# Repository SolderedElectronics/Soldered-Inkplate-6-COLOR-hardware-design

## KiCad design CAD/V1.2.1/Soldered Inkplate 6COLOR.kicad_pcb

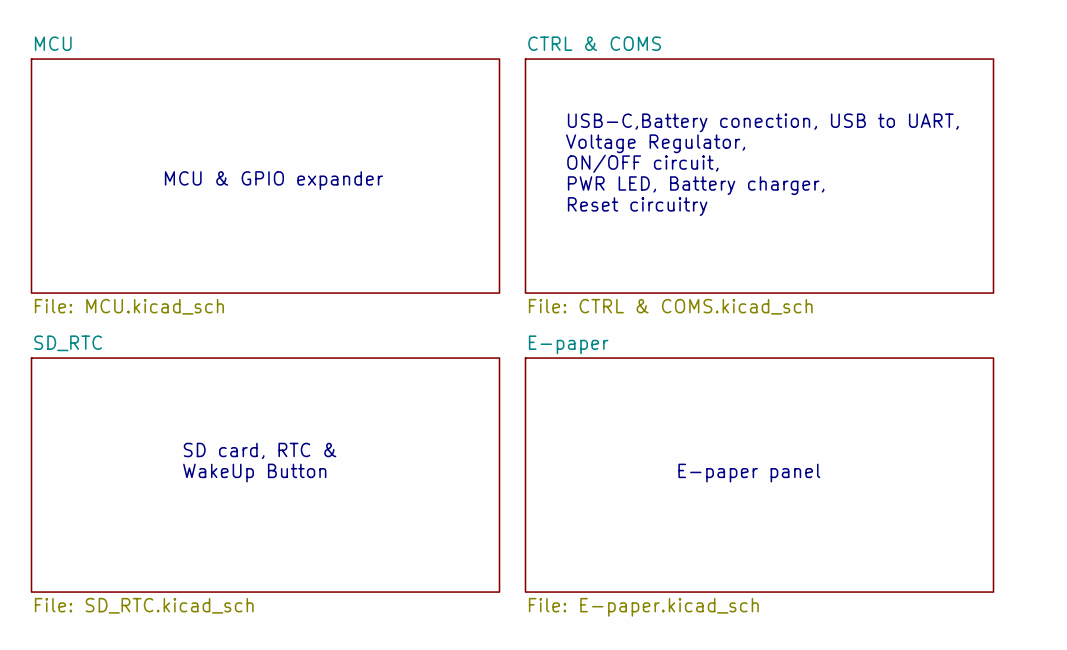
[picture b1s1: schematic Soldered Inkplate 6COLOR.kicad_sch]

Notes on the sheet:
MCU & GPIO expander
SD card, RTC & WakeUp Button
USB-C,Battery conection, USB to UART, Voltage Regulator, ON/OFF circuit, PWR LED, Battery charger, Reset circuitry
E-paper panel

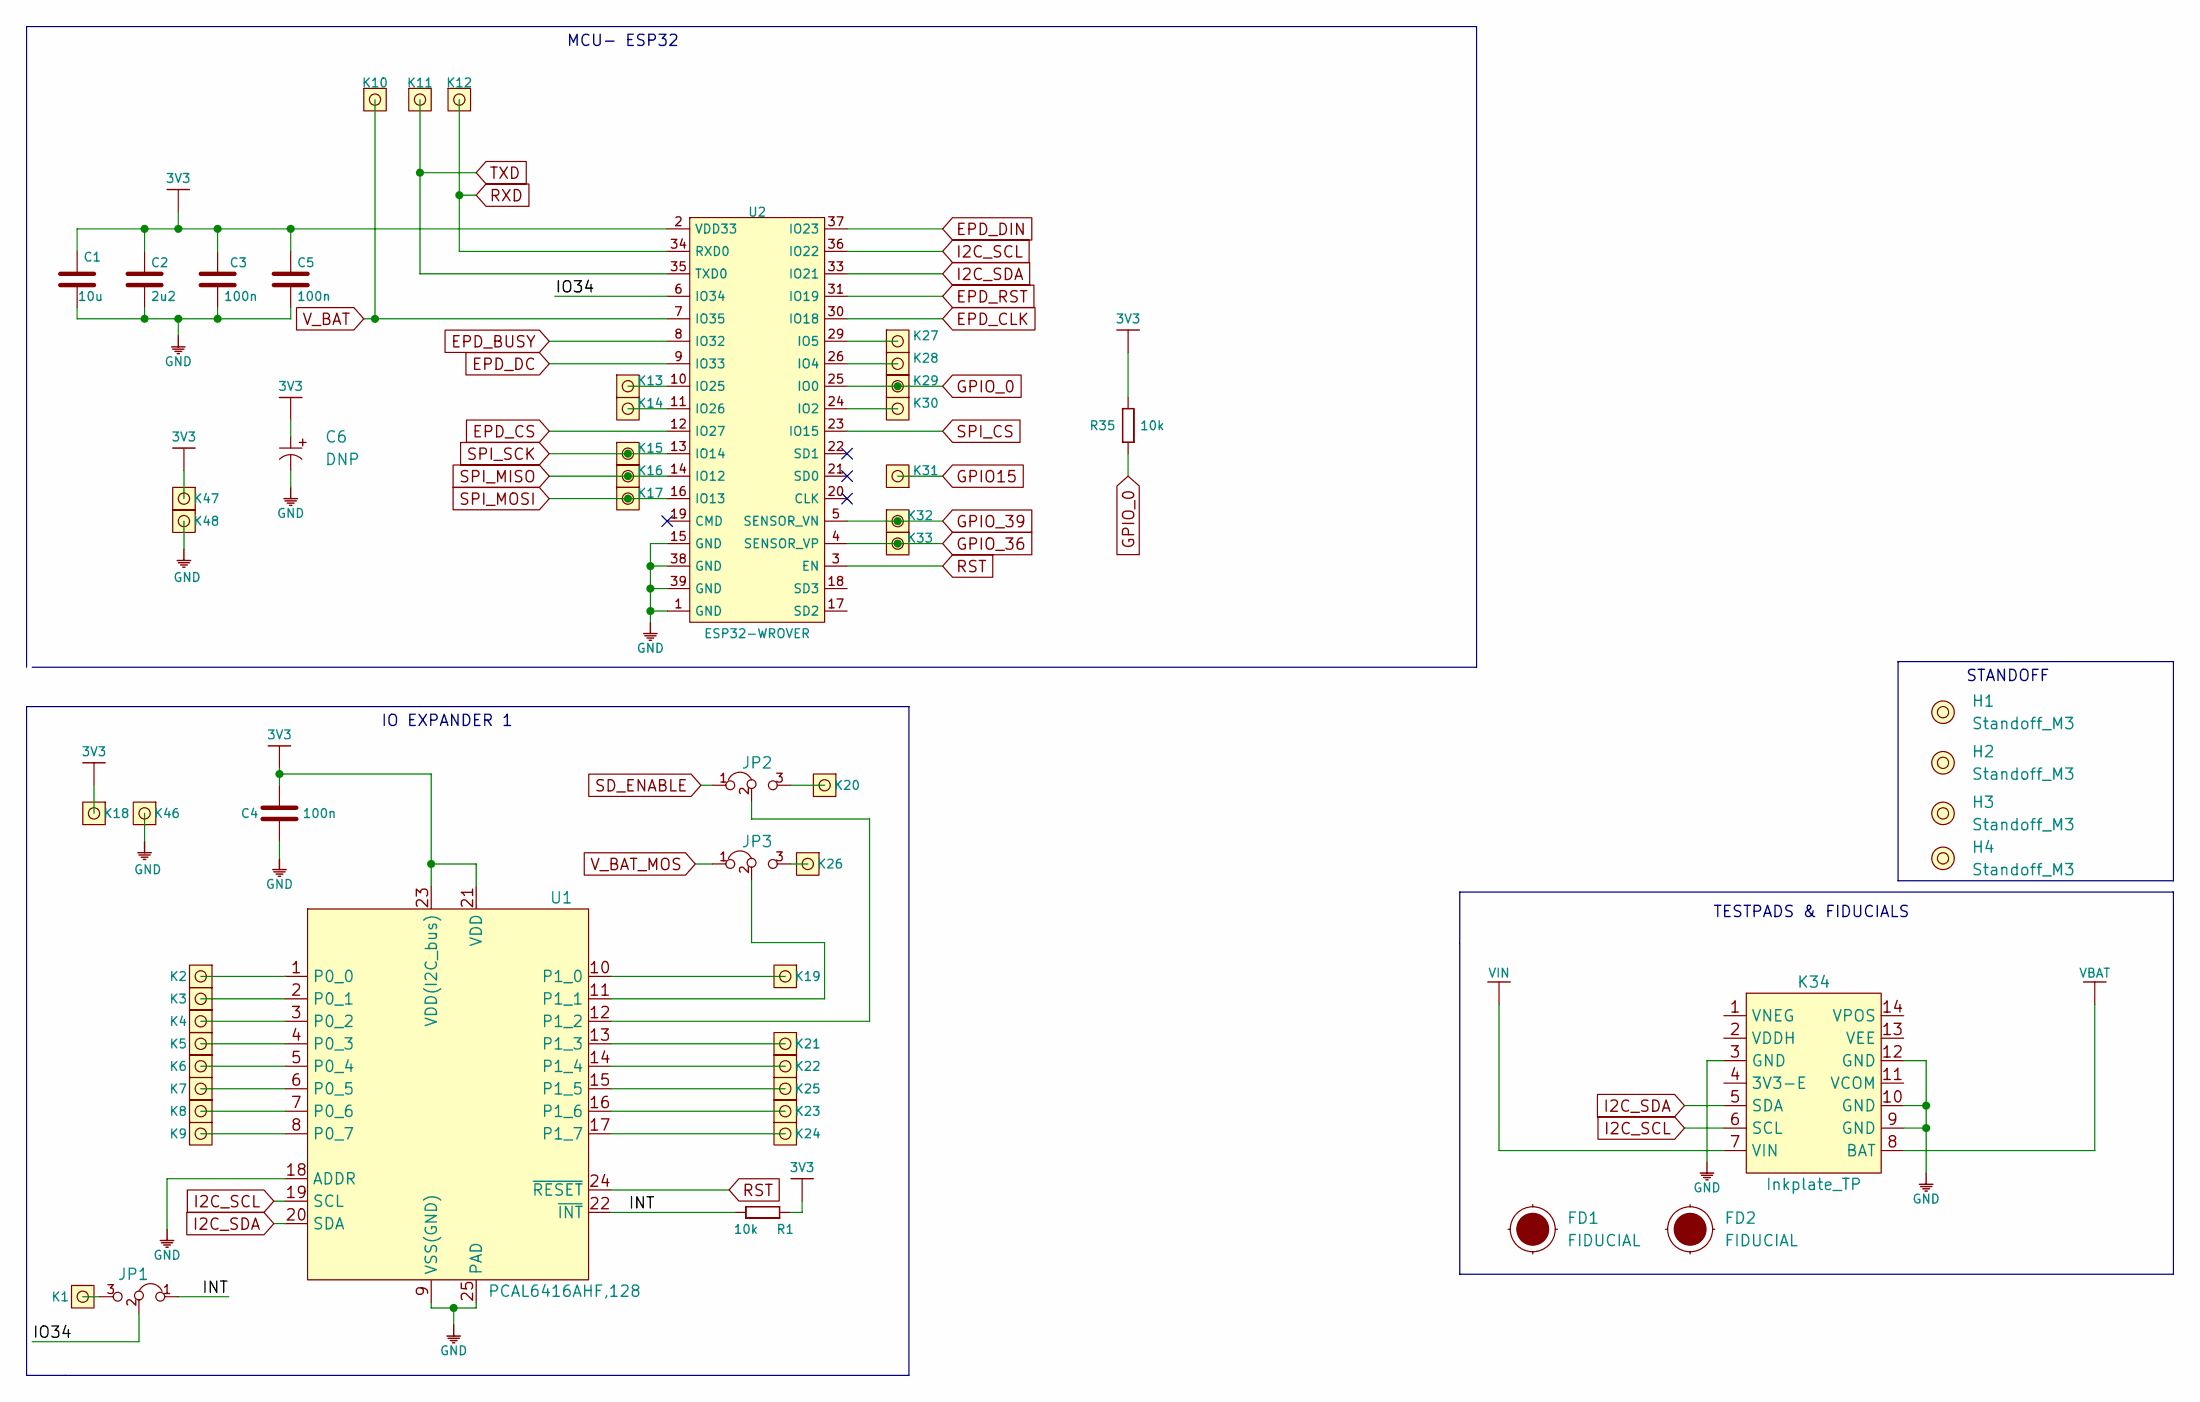
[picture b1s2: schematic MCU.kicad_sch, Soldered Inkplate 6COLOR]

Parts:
C1: 10u; 1206C
C2: 2u2; 0603C
C3, C4, C5: 100n; 0603C
C6: DNP; 2917C
FD1, FD2: FIDUCIAL; FIDUCIAL_23
H1, H2, H3, H4: Standoff_M3
JP1, JP2, JP3: SMD_JUMPER_3_PAD_CONNECTED_LEFT_TRACE
K1, K2, K3, K4, K5, K6, K7, K8, K9, K10, K11, K12, K13, K14, K15, K16, K17, K18, K19, K20, K21, K22, K23, K24, K25, K26, K27, K28, K29, K30, K31, K32, K33, K46, K47, K48: HEADER_MALE_1X1_Inkplate
K34: Inkplate_TP; INKPLATE TEST HEADER
R1, R35: 10k; 0603R
U1: PCAL6416AHF,128
U2: ESP32-WROVER

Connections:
3V3: C1.2, C2.2, C3.2, C4.2, C5.2, C6.1 (+), K18.1, K47.1, R1.1, R35.2, U1.21 (VDD), U1.23 (VDD(I2C_bus)), U2.2 (VDD33); also elsewhere on the board
/MCU/INT: JP1.1, R1.2, U1.22 (~INT)
/MCU/IO34: JP1.2, U2.6 (IO34)
EPD_BUSY: U2.8 (IO32); also elsewhere on the board
EPD_CLK: U2.30 (IO18); also elsewhere on the board
EPD_CS: U2.12 (IO27); also elsewhere on the board
EPD_DC: U2.9 (IO33); also elsewhere on the board
EPD_DIN: U2.37 (IO23); also elsewhere on the board
EPD_RST: U2.31 (IO19); also elsewhere on the board
GND: C1.1, C2.1, C3.1, C4.1, C5.1, C6.2 (-), K34.3 (GND), K34.9 (GND), K34.10 (GND), K34.12 (GND), K46.1, K48.1, U1.9 (VSS(GND)), U1.18 (ADDR), U1.25 (PAD), U2.1 (GND), U2.15 (GND), U2.38 (GND), U2.39 (GND); also elsewhere on the board
GPIO15: K31.1; also elsewhere on the board
GPIO_0: K29.1, R35.1, U2.25 (IO0); also elsewhere on the board
GPIO_36: K33.1, U2.4 (SENSOR_VP); also elsewhere on the board
GPIO_39: K32.1, U2.5 (SENSOR_VN); also elsewhere on the board
I2C_SCL: K34.6 (SCL), U1.19 (SCL), U2.36 (IO22); also elsewhere on the board
I2C_SDA: K34.5 (SDA), U1.20 (SDA), U2.33 (IO21); also elsewhere on the board
unnamed: JP1.3, K1.1
unnamed: JP2.2, U1.12 (P1_2)
unnamed: JP2.3, K20.1
unnamed: JP3.2, U1.11 (P1_1)
unnamed: JP3.3, K26.1
unnamed: K2.1, U1.1 (P0_0)
unnamed: K3.1, U1.2 (P0_1)
unnamed: K4.1, U1.3 (P0_2)
unnamed: K5.1, U1.4 (P0_3)
unnamed: K6.1, U1.5 (P0_4)
unnamed: K7.1, U1.6 (P0_5)
unnamed: K8.1, U1.7 (P0_6)
unnamed: K9.1, U1.8 (P0_7)
unnamed: K13.1, U2.10 (IO25)
unnamed: K14.1, U2.11 (IO26)
unnamed: K19.1, U1.10 (P1_0)
unnamed: K21.1, U1.13 (P1_3)
unnamed: K22.1, U1.14 (P1_4)
unnamed: K23.1, U1.16 (P1_6)
unnamed: K24.1, U1.17 (P1_7)
unnamed: K25.1, U1.15 (P1_5)
unnamed: K27.1, U2.29 (IO5)
unnamed: K28.1, U2.26 (IO4)
unnamed: K30.1, U2.24 (IO2)
RST: U1.24 (~RESET), U2.3 (EN); also elsewhere on the board
RXD: K12.1, U2.34 (RXD0); also elsewhere on the board
SD_ENABLE: JP2.1; also elsewhere on the board
SPI_CS: U2.23 (IO15); also elsewhere on the board
SPI_MISO: K16.1, U2.14 (IO12); also elsewhere on the board
SPI_MOSI: K17.1, U2.16 (IO13); also elsewhere on the board
SPI_SCK: K15.1, U2.13 (IO14); also elsewhere on the board
TXD: K11.1, U2.35 (TXD0); also elsewhere on the board
VBAT: K34.8 (BAT); also elsewhere on the board
VIN: K34.7 (VIN); also elsewhere on the board
V_BAT: K10.1, U2.7 (IO35); also elsewhere on the board
V_BAT_MOS: JP3.1; also elsewhere on the board

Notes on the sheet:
IO EXPANDER 1
MCU- ESP32
TESTPADS & FIDUCIALS
STANDOFF

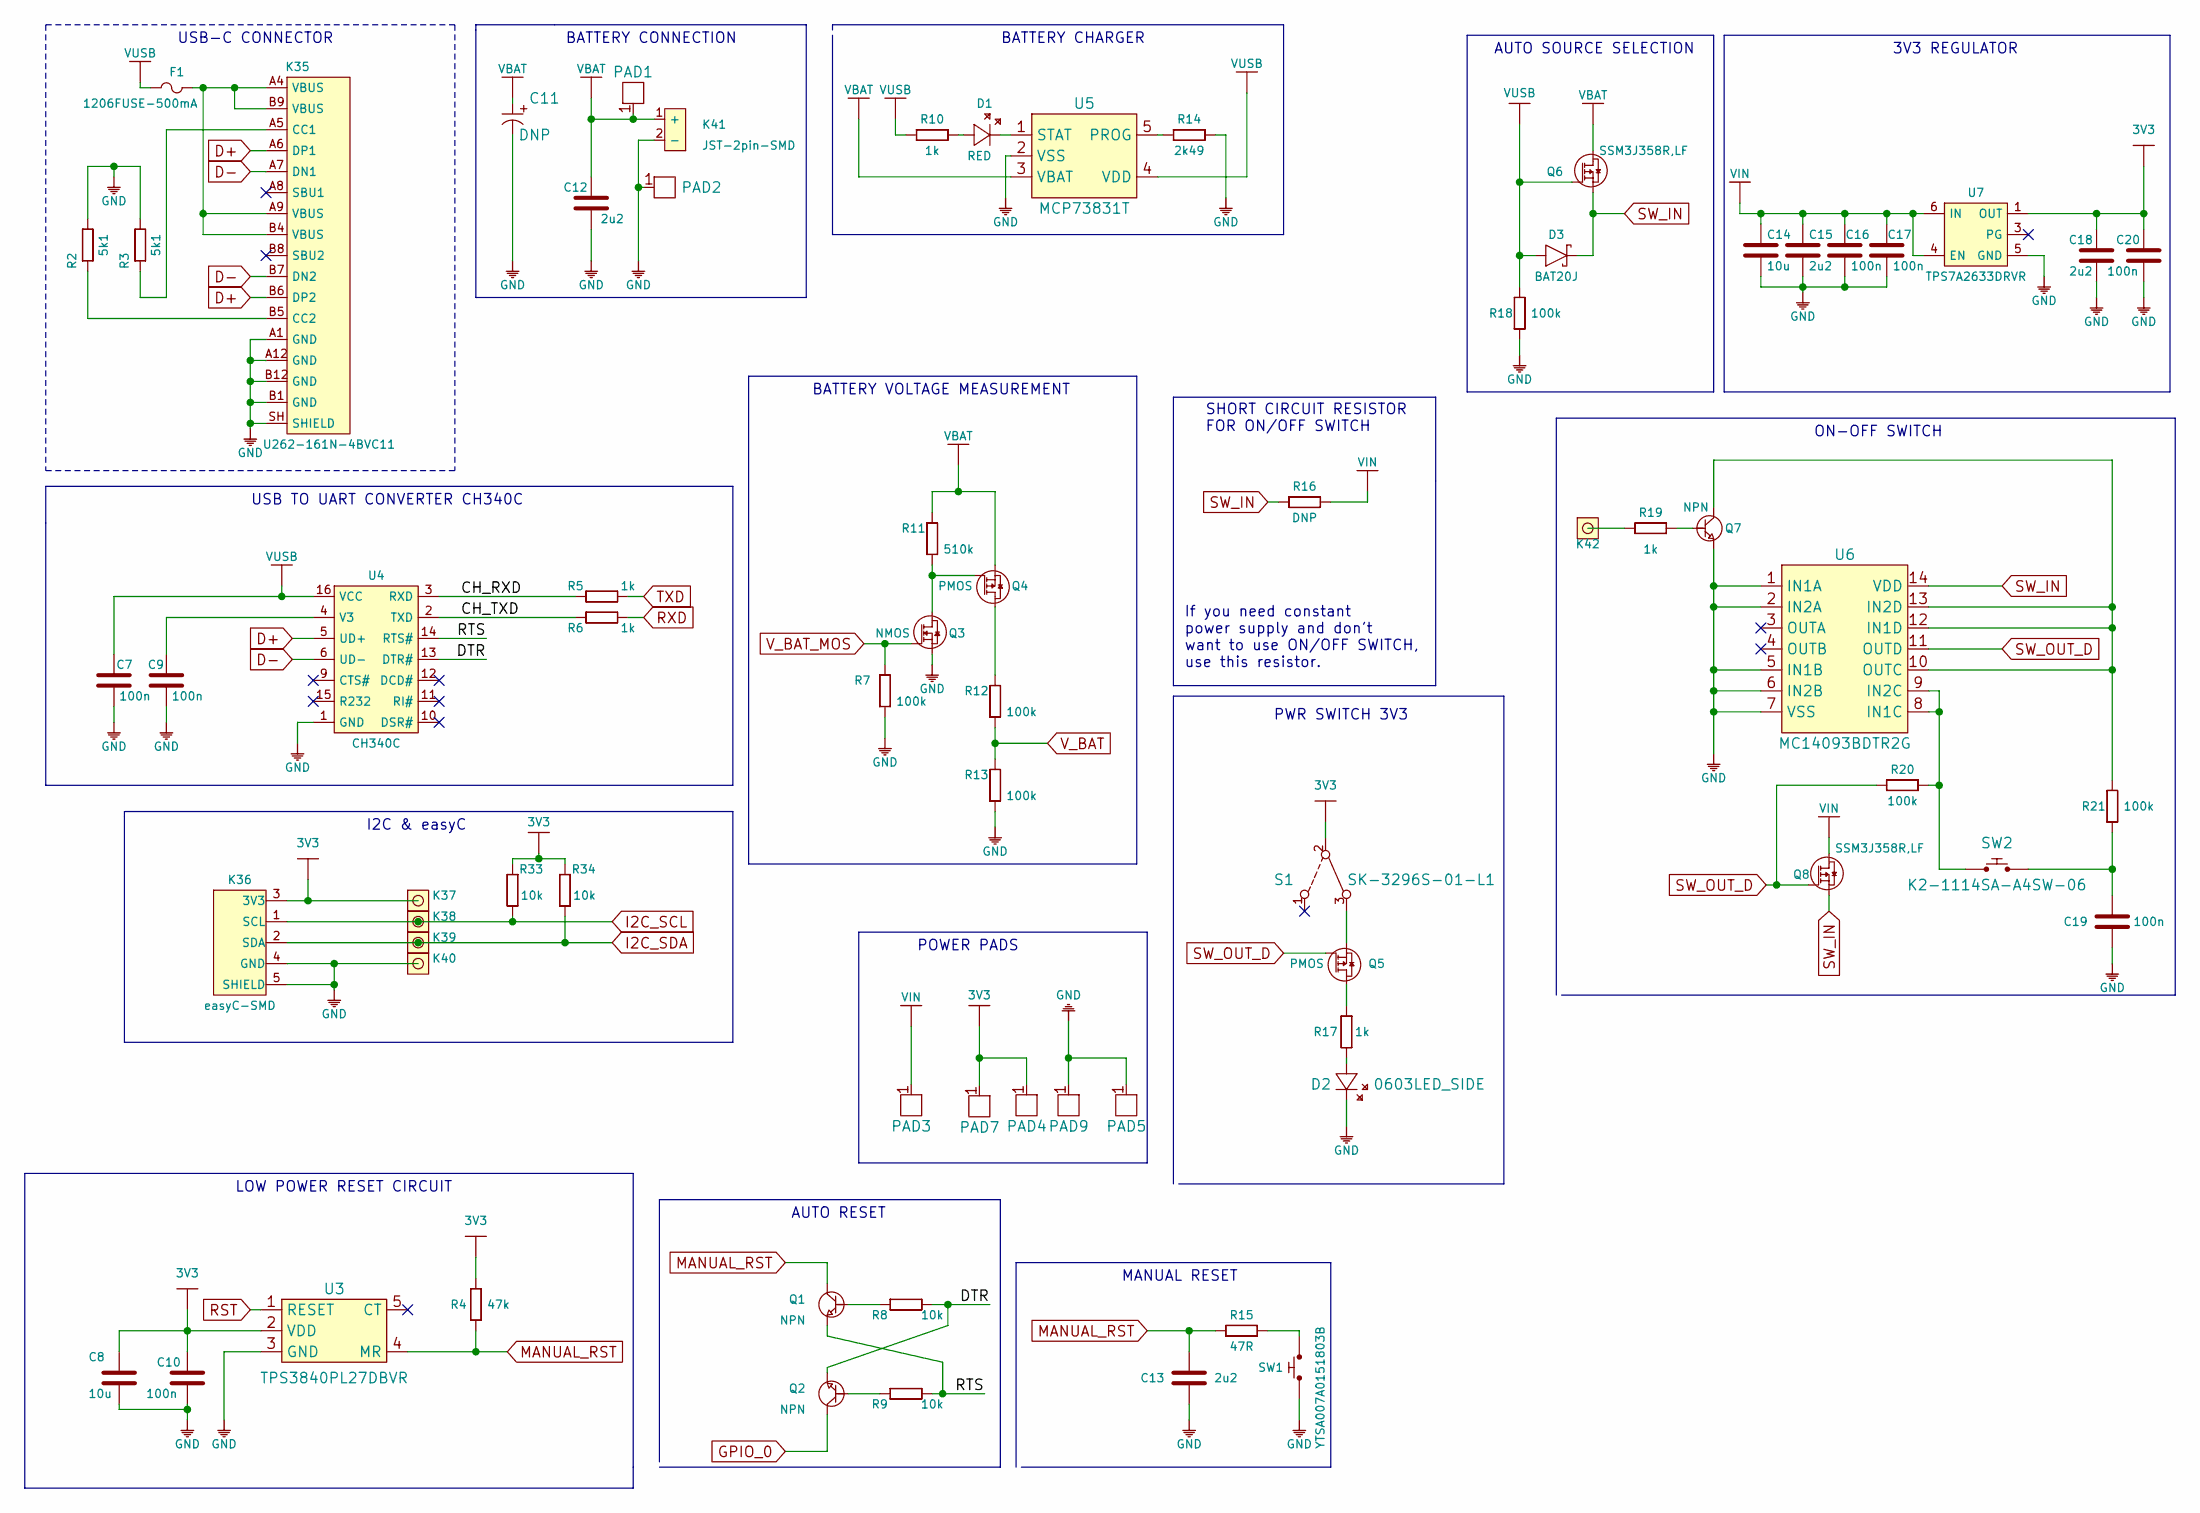
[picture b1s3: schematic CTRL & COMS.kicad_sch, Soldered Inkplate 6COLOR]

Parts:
C7, C9, C10, C16, C17, C19, C20: 100n; 0603C
C8, C14: 10u; 1206C
C11: DNP; 2917C
C12, C13, C15, C18: 2u2; 0603C
D1: RED; 0402LED
D2: 0603LED_SIDE; LTST-S270GKT
D3: BAT20J; SOD-323
F1: 1206FUSE-500mA; 1206FUSE
K35: U262-161N-4BVC11
K36: easyC-SMD; easyC-connector
K37, K38, K39, K40, K42: HEADER_MALE_1X1_Inkplate
K41: JST-2pin-SMD
PAD1, PAD2, PAD3, PAD4, PAD5, PAD7, PAD9: PAD_4x4
Q1, Q2, Q7: NPN; SOT-23-3
Q3: NMOS; SOT-23-3
Q4, Q5: PMOS; SOT-23-3
Q6, Q8: SSM3J358R,LF; SOT-23-3
R2, R3: 5k1; 0603R
R4: 47k; 0603R
R5, R6, R10, R17, R19: 1k; 0603R
R7, R12, R13, R18, R20, R21: 100k; 0603R
R8, R9, R33, R34: 10k; 0603R
R11: 510k; 0603R
R14: 2k49; 0603R
R15: 47R; 0603R
R16: DNP; 0603R
S1: SK-3296S-01-L1
SW1: YTSA007A0151803B
SW2: K2-1114SA-A4SW-06
U3: TPS3840PL27DBVR; SOT-23-5
U4: CH340C; SOP-16
U5: MCP73831T; SOT-23-5
U6: MC14093BDTR2G; TSSOP-14
U7: TPS7A2633DRVR

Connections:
3V3: C8.2, C10.2, C18.2, C20.2, K36.3 (3V3), K37.1, PAD4.1, PAD7.1, R4.2, R33.1, R34.1, S1.2, U3.2 (VDD), U7.1 (OUT); also elsewhere on the board
/CTRL & COMS/CH_RXD: R5.1, U4.3 (RXD)
/CTRL & COMS/CH_TXD: R6.1, U4.2 (TXD)
/CTRL & COMS/DTR: Q2.2 (E), R8.2, U4.13 (DTR#)
/CTRL & COMS/RTS: Q1.2 (E), R9.2, U4.14 (RTS#)
D+: K35.A6 (DP1), K35.B6 (DP2), U4.5 (UD+)
D-: K35.A7 (DN1), K35.B7 (DN2), U4.6 (UD-)
GND: C7.1, C8.1, C9.1, C10.1, C11.2 (-), C12.1, C13.1, C14.1, C15.1, C16.1, C17.1, C18.1, C19.1, C20.1, D2.2 (K), K35.A1 (GND), K35.A12 (GND), K35.B1 (GND), K35.B12 (GND), K35.SH (SHIELD), K36.4 (GND), K36.5 (SHIELD), K40.1, K41.2 (-), PAD2.1, PAD5.1, PAD9.1, Q3.2 (S), Q7.2 (E), R2.2, R3.2, R7.1, R13.1, R14.2, R18.1, SW1.1, U3.3 (GND), U4.1 (GND), U5.2 (VSS), U6.1 (IN1A), U6.2 (IN2A), U6.5 (IN1B), U6.6 (IN2B), U6.7 (VSS), U7.5 (GND); also elsewhere on the board
GPIO_0: Q2.3 (C); also elsewhere on the board
I2C_SCL: K36.1 (SCL), K38.1, R33.2; also elsewhere on the board
I2C_SDA: K36.2 (SDA), K39.1, R34.2; also elsewhere on the board
MANUAL_RST: C13.2, Q1.3 (C), R4.1, R15.2, U3.4 (MR)
unnamed: C9.2, U4.4 (V3)
unnamed: C19.2, R21.1, SW2.2
unnamed: D1.1 (A), R10.2
unnamed: D1.2 (K), U5.1 (STAT)
unnamed: D2.1 (A), R17.2
unnamed: F1.2, K35.A4 (VBUS), K35.A9 (VBUS), K35.B4 (VBUS), K35.B9 (VBUS)
unnamed: K35.A5 (CC1), R3.1
unnamed: K35.B5 (CC2), R2.1
unnamed: K42.1, R19.2
unnamed: Q1.1 (B), R8.1
unnamed: Q2.1 (B), R9.1
unnamed: Q3.3 (D), Q4.1 (G), R11.1
unnamed: Q4.3 (D), R12.2
unnamed: Q5.2 (S), S1.3
unnamed: Q5.3 (D), R17.1
unnamed: Q7.1 (B), R19.1
unnamed: Q7.3 (C), R21.2, U6.10 (OUTC), U6.12 (IN1D), U6.13 (IN2D)
unnamed: R14.1, U5.5 (PROG)
unnamed: R15.1, SW1.2
unnamed: R20.1, SW2.1, U6.8 (IN1C), U6.9 (IN2C)
RST: U3.1 (RESET); also elsewhere on the board
RXD: R6.2; also elsewhere on the board
SW_IN: D3.2 (C), Q6.2 (S), Q8.2 (S), R16.1, U6.14 (VDD)
SW_OUT_D: Q5.1 (G), Q8.1 (G), R20.2, U6.11 (OUTD)
TXD: R5.2; also elsewhere on the board
VBAT: C11.1 (+), C12.2, K41.1 (+), PAD1.1, Q4.2 (S), Q6.3 (D), R11.2, U5.3 (VBAT); also elsewhere on the board
VIN: C14.2, C15.2, C16.2, C17.2, PAD3.1, Q8.3 (D), R16.2, U7.4 (EN), U7.6 (IN); also elsewhere on the board
VUSB: C7.2, D3.1 (A), F1.1, Q6.1 (G), R10.1, R18.2, U4.16 (VCC), U5.4 (VDD)
V_BAT: R12.1, R13.2; also elsewhere on the board
V_BAT_MOS: Q3.1 (G), R7.2; also elsewhere on the board

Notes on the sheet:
AUTO RESET
LOW POWER RESET CIRCUIT
ON-OFF SWITCH
POWER PADS
SHORT CIRCUIT RESISTOR FOR ON/OFF SWITCH
3V3 REGULATOR
USB TO UART CONVERTER CH340C
BATTERY VOLTAGE MEASUREMENT
If you need constant power supply and don't want to use ON/OFF SWITCH, use this resistor.
BATTERY CONNECTION
MANUAL RESET
PWR SWITCH 3V3
USB-C CONNECTOR
AUTO SOURCE SELECTION
I2C & easyC
BATTERY CHARGER

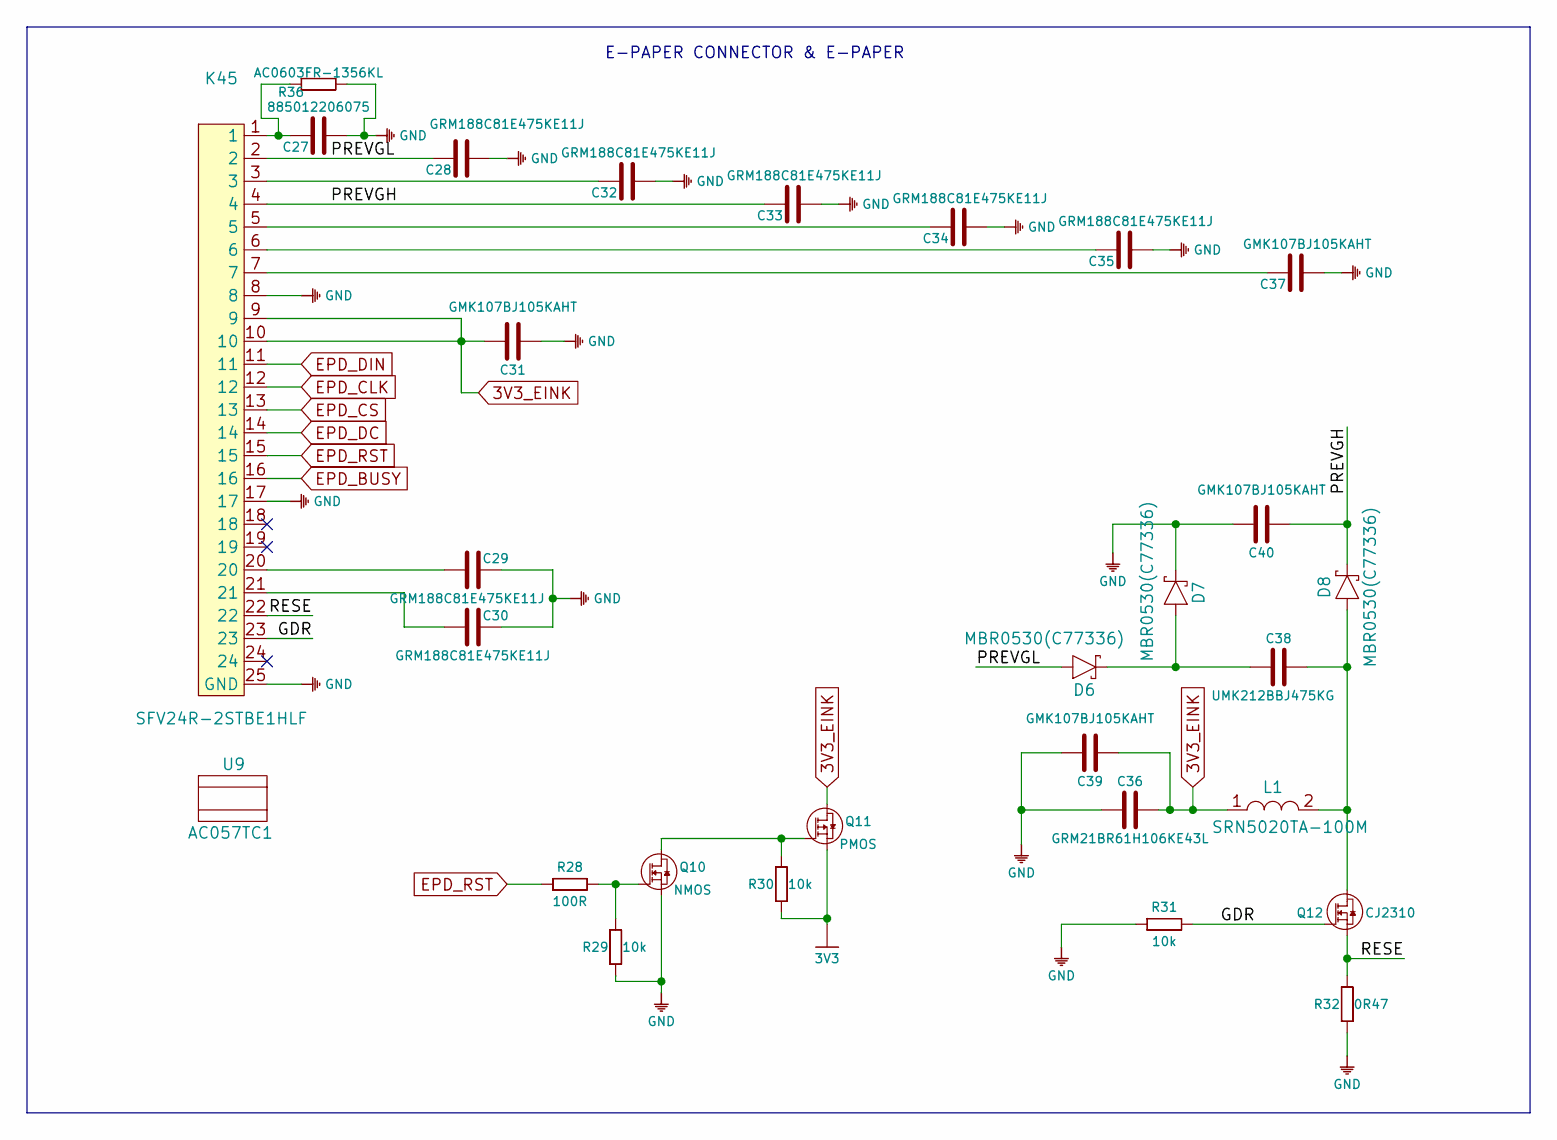
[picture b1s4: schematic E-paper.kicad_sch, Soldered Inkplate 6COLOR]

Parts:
C27: 885012206075; 0603C
C28, C29, C30, C32, C33, C34, C35: GRM188C81E475KE11J; 0603C
C31, C37, C39, C40: GMK107BJ105KAHT; 0603C
C36: GRM21BR61H106KE43L; 0805C
C38: UMK212BBJ475KG; 0805C
D6, D7, D8: MBR0530(C77336); SOD−123
K45: SFV24R-2STBE1HLF
L1: SRN5020TA-100M; SRN5020TA-2R2M
Q10: NMOS; SOT-23-3
Q11: PMOS; SOT-23-3
Q12: CJ2310; SOT-23-3
R28: 100R; 0603R
R29, R30, R31: 10k; 0603R
R32: 0R47; 0603R
R36: AC0603FR-1356KL; 0603R
U9: AC057TC1

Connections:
3V3: Q11.2 (S), R30.1; also elsewhere on the board
3V3_EINK: C31.1, C36.2, C39.2, K45.9, K45.10, L1.1, Q11.3 (D)
/E-paper/GDR: K45.23, Q12.1 (G), R31.2
/E-paper/PREVGH: C33.1, C40.2, D8.1 (C), K45.4
/E-paper/PREVGL: C28.1, D6.2 (A), K45.2
/E-paper/RESE: K45.22, Q12.2 (S), R32.2
EPD_BUSY: K45.16; also elsewhere on the board
EPD_CLK: K45.12; also elsewhere on the board
EPD_CS: K45.13; also elsewhere on the board
EPD_DC: K45.14; also elsewhere on the board
EPD_DIN: K45.11; also elsewhere on the board
EPD_RST: K45.15, R28.1; also elsewhere on the board
GND: C27.2, C28.2, C29.2, C30.2, C31.2, C32.2, C33.2, C34.2, C35.2, C36.1, C37.2, C39.1, C40.1, D7.1 (C), K45.8, K45.17, K45.25 (GND), Q10.2 (S), R29.1, R31.1, R32.1, R36.2; also elsewhere on the board
unnamed: C27.1, K45.1, R36.1
unnamed: C29.1, K45.20
unnamed: C30.1, K45.21
unnamed: C32.1, K45.3
unnamed: C34.1, K45.5
unnamed: C35.1, K45.6
unnamed: C37.1, K45.7
unnamed: C38.1, D6.1 (C), D7.2 (A)
unnamed: C38.2, D8.2 (A), L1.2, Q12.3 (D)
unnamed: Q10.1 (G), R28.2, R29.2
unnamed: Q10.3 (D), Q11.1 (G), R30.2

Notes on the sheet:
E-PAPER CONNECTOR & E-PAPER

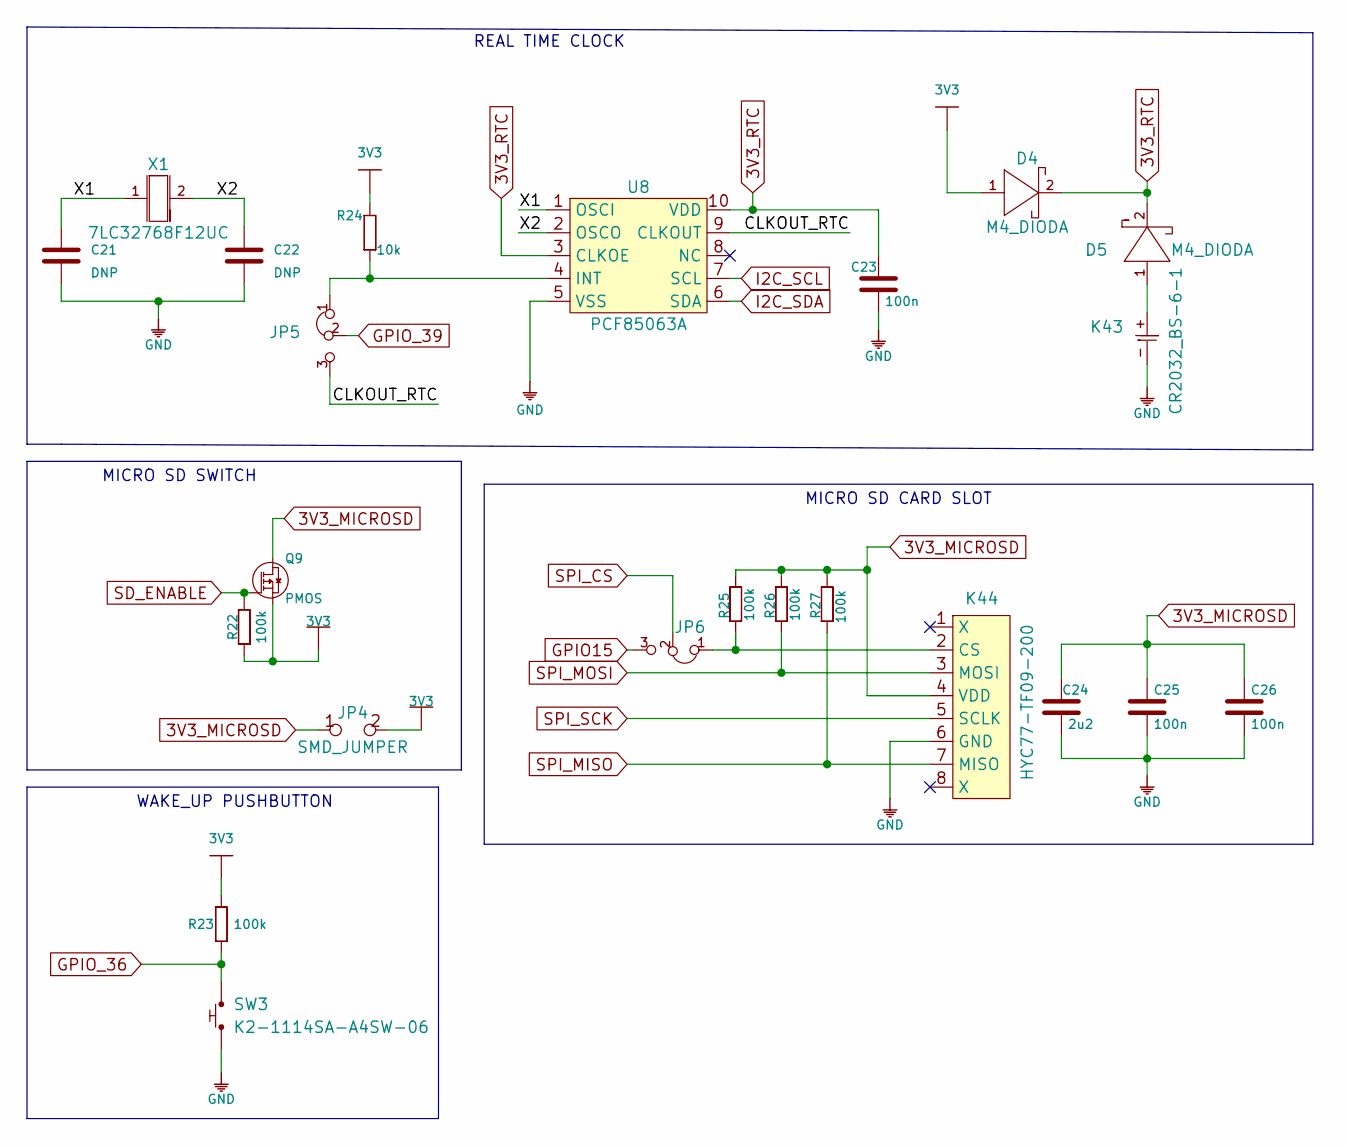
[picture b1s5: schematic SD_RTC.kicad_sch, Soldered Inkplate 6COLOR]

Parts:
C21, C22: DNP; 0603C
C23, C25, C26: 100n; 0603C
C24: 2u2; 0603C
D4, D5: M4_DIODA
JP4: SMD_JUMPER
JP5, JP6: SMD_JUMPER_3_PAD_CONNECTED_LEFT_TRACE
K43: CR2032_BS-6-1; CR2032-BS-6-1
K44: HYC77-TF09-200
Q9: PMOS; SOT-23-3
R22, R23, R25, R26, R27: 100k; 0603R
R24: 10k; 0603R
SW3: K2-1114SA-A4SW-06
U8: PCF85063A
X1: 7LC32768F12UC; ABS07AIG-32.768KHZ-7-D-T

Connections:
3V3: D4.1 (A), JP4.2, Q9.2 (S), R22.1, R23.2, R24.2; also elsewhere on the board
3V3_MICROSD: C24.2, C25.2, C26.2, JP4.1, K44.4 (VDD), Q9.3 (D), R25.2, R26.2, R27.2
3V3_RTC: C23.2, D4.2 (K), D5.2 (K), U8.3 (CLKOE), U8.10 (VDD)
/SD_RTC/CLKOUT_RTC: JP5.3, U8.9 (CLKOUT)
/SD_RTC/X1: C21.2, U8.1 (OSCI), X1.1
/SD_RTC/X2: C22.2, U8.2 (OSCO), X1.2
GND: C21.1, C22.1, C23.1, C24.1, C25.1, C26.1, K43.-, K44.6 (GND), SW3.1, U8.5 (VSS); also elsewhere on the board
GPIO15: JP6.3; also elsewhere on the board
GPIO_36: R23.1, SW3.2; also elsewhere on the board
GPIO_39: JP5.2; also elsewhere on the board
I2C_SCL: U8.7 (SCL); also elsewhere on the board
I2C_SDA: U8.6 (SDA); also elsewhere on the board
unnamed: D5.1 (A), K43.+
unnamed: JP5.1, R24.1, U8.4 (INT)
unnamed: JP6.1, K44.2 (CS), R25.1
SD_ENABLE: Q9.1 (G), R22.2; also elsewhere on the board
SPI_CS: JP6.2; also elsewhere on the board
SPI_MISO: K44.7 (MISO), R27.1; also elsewhere on the board
SPI_MOSI: K44.3 (MOSI), R26.1; also elsewhere on the board
SPI_SCK: K44.5 (SCLK); also elsewhere on the board

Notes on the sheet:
MICRO SD CARD SLOT
WAKE_UP PUSHBUTTON
REAL TIME CLOCK
MICRO SD SWITCH

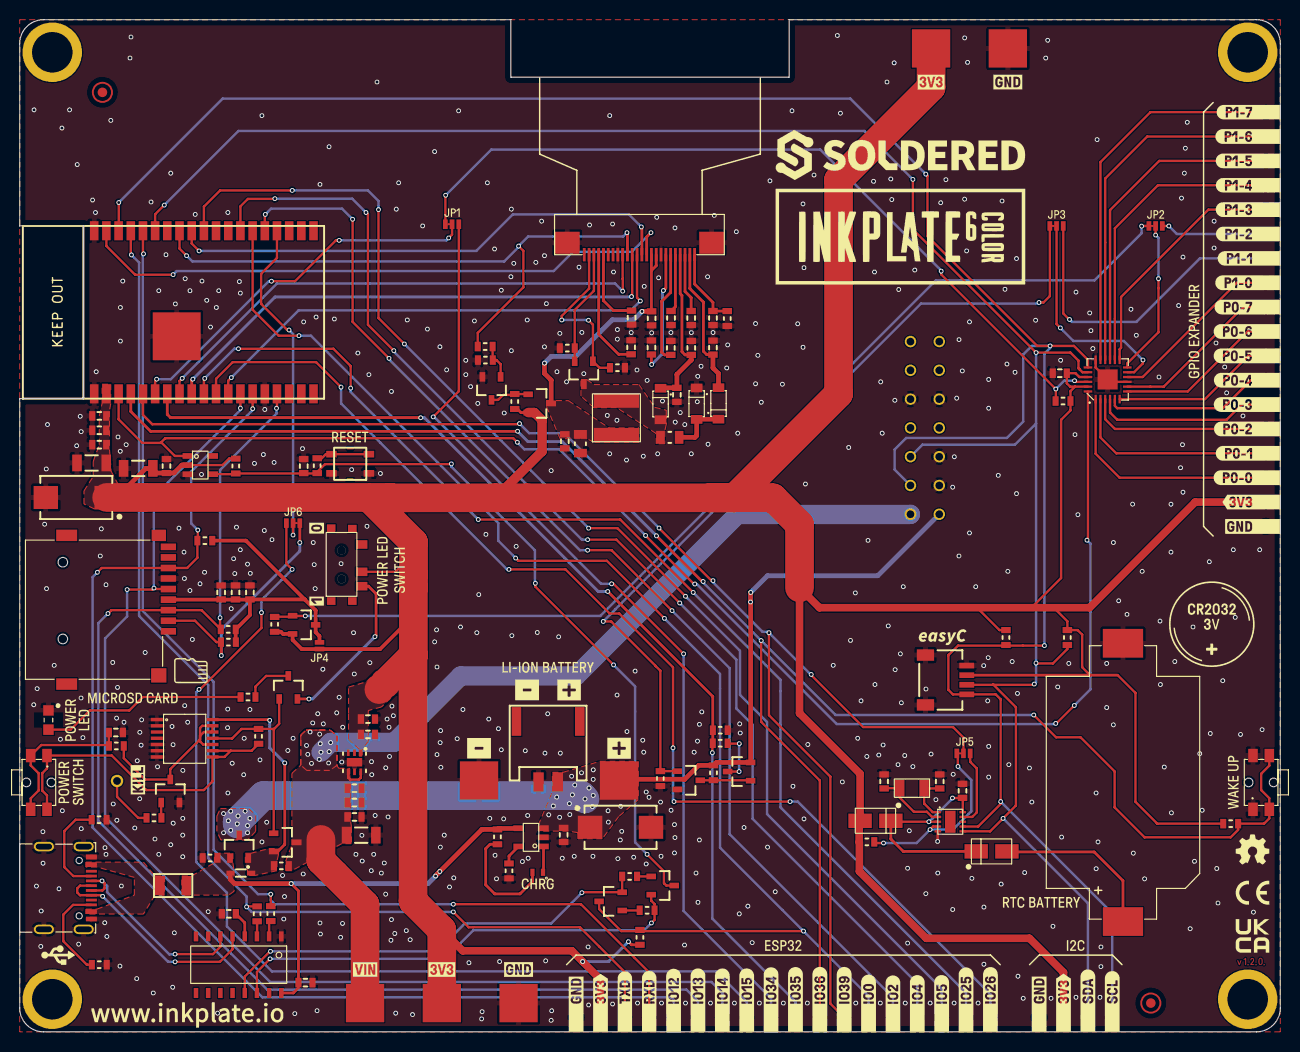
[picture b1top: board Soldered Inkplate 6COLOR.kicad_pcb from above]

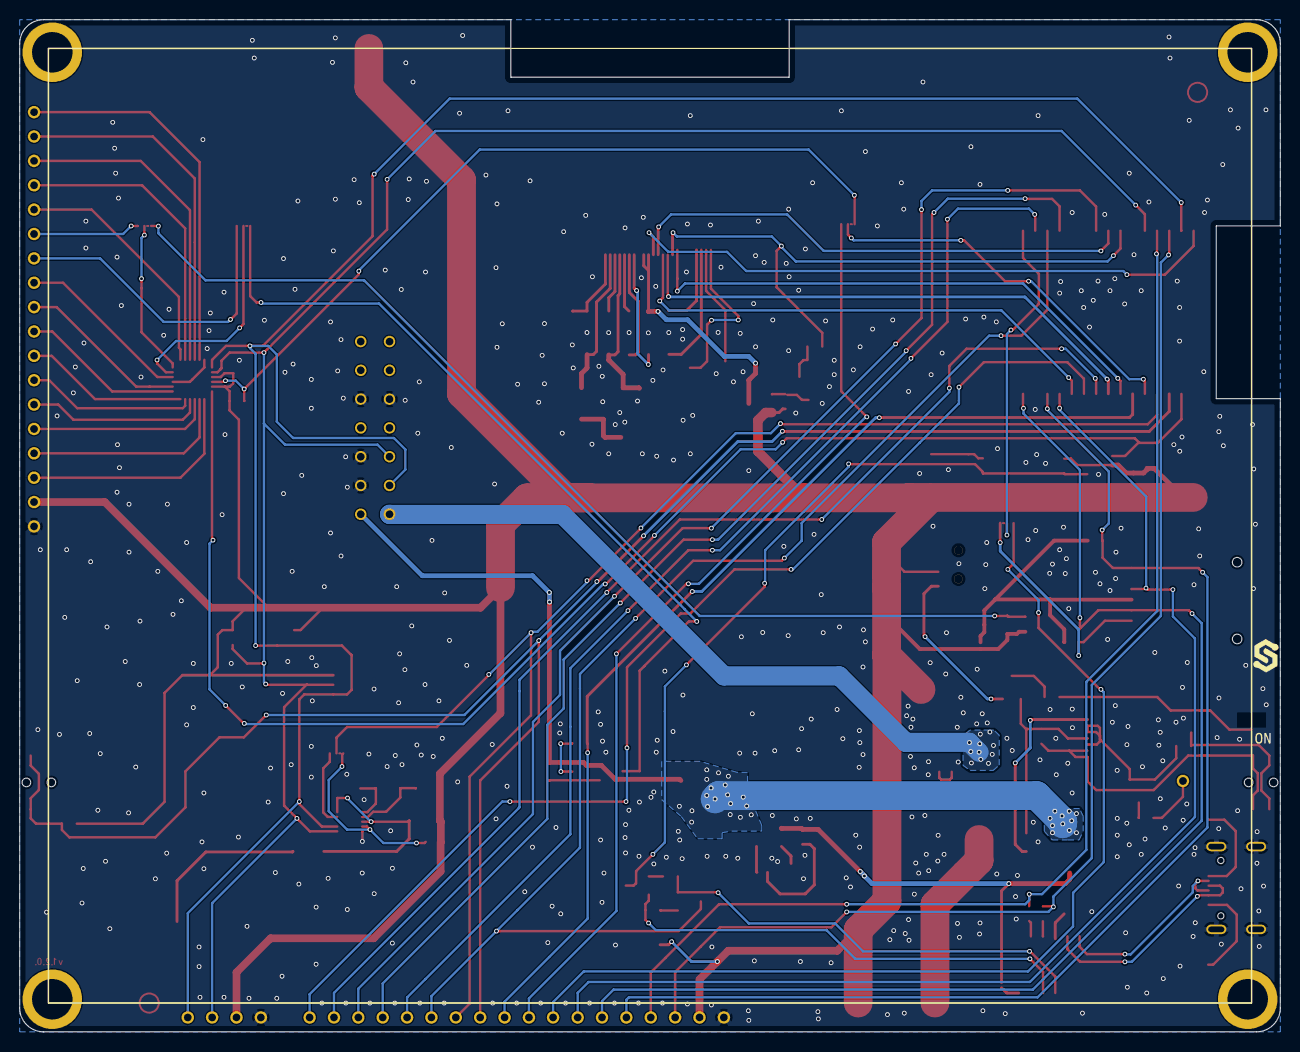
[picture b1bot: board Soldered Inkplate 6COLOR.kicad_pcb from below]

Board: 2 copper layers, 131.4 x 105.5 mm, 253 parts (2 on the bottom side), 106 nets.

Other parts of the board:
kibuzzard-62FF3A3F: G***; kibuzzard-62FF3A3F
kibuzzard-62FF3A7A: G***; kibuzzard-62FF3A7A
kibuzzard-62FF3A09: G***; kibuzzard-62FF3A09
kibuzzard-62FF3A16: G***; kibuzzard-62FF3A16
kibuzzard-62FF3A28: G***; kibuzzard-62FF3A28
kibuzzard-62FF3A33: G***; kibuzzard-62FF3A33
kibuzzard-62FF3A67: G***; kibuzzard-62FF3A67
kibuzzard-62FF3A87: G***; kibuzzard-62FF3A87
kibuzzard-62FF3A95: G***; kibuzzard-62FF3A95
kibuzzard-62FF3AA5: G***; kibuzzard-62FF3AA5
kibuzzard-62FF3AB1: G***; kibuzzard-62FF3AB1
kibuzzard-62FF3AC7: G***; kibuzzard-62FF3AC7
kibuzzard-62FF3AD5: G***; kibuzzard-62FF3AD5
kibuzzard-62FF3DBA: G***; kibuzzard-62FF3DBA
kibuzzard-62FF3E47: G***; kibuzzard-62FF3E47
kibuzzard-62FF3E62: G***; kibuzzard-62FF3E62
kibuzzard-62FF3EAF: G***; kibuzzard-62FF3EAF
kibuzzard-62FF3F46: G***; kibuzzard-62FF3F46
kibuzzard-62FF3F61: G***; kibuzzard-62FF3F61
kibuzzard-62FF3F79: G***; kibuzzard-62FF3F79
kibuzzard-62FF3F95: G***; kibuzzard-62FF3F95
kibuzzard-62FF3FB7: G***; kibuzzard-62FF3FB7
kibuzzard-62FF3FFC: G***; kibuzzard-62FF3FFC
kibuzzard-62FF39B7: G***; kibuzzard-62FF39B7
kibuzzard-62FF39E3: G***; kibuzzard-62FF39E3
kibuzzard-62FF39F5: G***; kibuzzard-62FF39F5
kibuzzard-62FF380F: G***; kibuzzard-62FF380F
kibuzzard-62FF3822: G***; kibuzzard-62FF3822
kibuzzard-630C9D2C: G***; kibuzzard-630C9D2C
kibuzzard-630C992F: G***; kibuzzard-630C992F
kibuzzard-630C9914: G***; kibuzzard-630C9914
kibuzzard-630F4237: G***; kibuzzard-630F4237
kibuzzard-637B42A1: G***; kibuzzard-637B42A1
kibuzzard-637B42AC: G***; kibuzzard-637B42AC
kibuzzard-637B42BE: G***; kibuzzard-637B42BE
kibuzzard-637B42CB: G***; kibuzzard-637B42CB
kibuzzard-637B42EA: G***; kibuzzard-637B42EA
kibuzzard-637B42FA: G***; kibuzzard-637B42FA
kibuzzard-637B43A5: G***; kibuzzard-637B43A5
kibuzzard-637B43B3: G***; kibuzzard-637B43B3
kibuzzard-637B43FB: G***; kibuzzard-637B43FB
kibuzzard-637B44AA: G***; kibuzzard-637B44AA
kibuzzard-637B44BD: G***; kibuzzard-637B44BD
kibuzzard-637B44FE: G***; kibuzzard-637B44FE
kibuzzard-637B428F, kibuzzard-637B428F#2: G***; kibuzzard-637B428F
kibuzzard-637B430F: G***; kibuzzard-637B430F
kibuzzard-637B431F: G***; kibuzzard-637B431F
kibuzzard-637B433E: G***; kibuzzard-637B433E
kibuzzard-637B434C: G***; kibuzzard-637B434C
kibuzzard-637B4274, kibuzzard-637B4274#2: G***; kibuzzard-637B4274
kibuzzard-637B4330: G***; kibuzzard-637B4330
kibuzzard-637B4364: G***; kibuzzard-637B4364
kibuzzard-637B4385: G***; kibuzzard-637B4385
kibuzzard-637B4394: G***; kibuzzard-637B4394
kibuzzard-638085AE: G***; kibuzzard-638085AE
kibuzzard-638085B8: G***; kibuzzard-638085B8
kibuzzard-638085C4: G***; kibuzzard-638085C4
kibuzzard-638085D8: G***; kibuzzard-638085D8
kibuzzard-638085E0: G***; kibuzzard-638085E0
kibuzzard-638085EF: G***; kibuzzard-638085EF
kibuzzard-638085FC: G***; kibuzzard-638085FC
kibuzzard-638086A4: G***; kibuzzard-638086A4
kibuzzard-638086FC: G***; kibuzzard-638086FC
kibuzzard-6380860A: G***; kibuzzard-6380860A
kibuzzard-6393034C: G***; kibuzzard-6393034C
kibuzzard-6393035D: G***; kibuzzard-6393035D
kibuzzard-63808589: G***; kibuzzard-63808589
kibuzzard-63808619: G***; kibuzzard-63808619
kibuzzard-63808621: G***; kibuzzard-63808621
kibuzzard-63809971: G***; kibuzzard-63809971
kibuzzard-63930309: G***; kibuzzard-63930309
kibuzzard-63930326: G***; kibuzzard-63930326

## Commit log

2023-06-21 Updating open source files.
